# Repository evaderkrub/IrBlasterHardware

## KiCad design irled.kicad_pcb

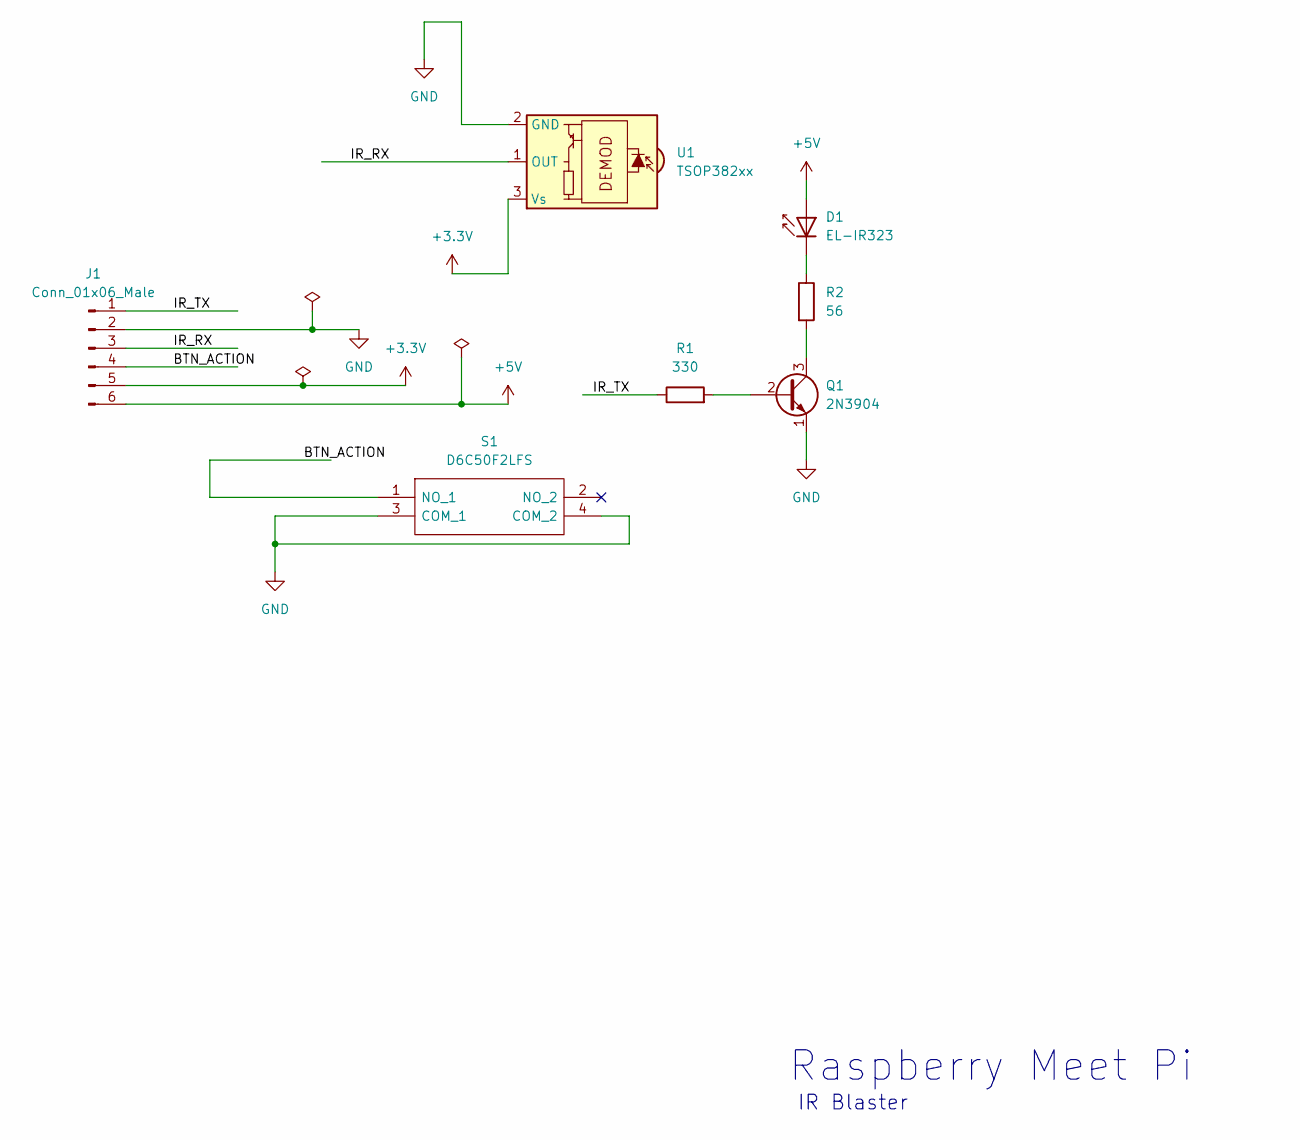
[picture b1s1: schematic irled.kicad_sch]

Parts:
D1: EL-IR323; LED_D5.0mm_IRGrey
J1: Conn_01x06_Male; PinHeader_1x06_P2.54mm_Vertical
Q1: 2N3904; TO-92_Inline
R1: 330; R_Axial_DIN0207_L6.3mm_D2.5mm_P10.16mm_Horizontal
R2: 56; R_Axial_DIN0309_L9.0mm_D3.2mm_P12.70mm_Horizontal
S1: D6C50F2LFS; Mouser Part Number 611-D6C50F2LFS
U1: TSOP382xx; Vishay_MINICAST-3Pin

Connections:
+3V3: J1.5, U1.3 (Vs)
+5V: D1.2 (A), J1.6
/BTN_ACTION: J1.4, S1.1 (NO_1)
/IR_RX: J1.3, U1.1 (OUT)
/IR_TX: J1.1, R1.1
GND: J1.2, Q1.1 (E), S1.3 (COM_1), S1.4 (COM_2), U1.2 (GND)
unnamed: D1.1 (K), R2.1
unnamed: Q1.2 (B), R1.2
unnamed: Q1.3 (C), R2.2

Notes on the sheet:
IR Blaster
Raspberry Meet Pi

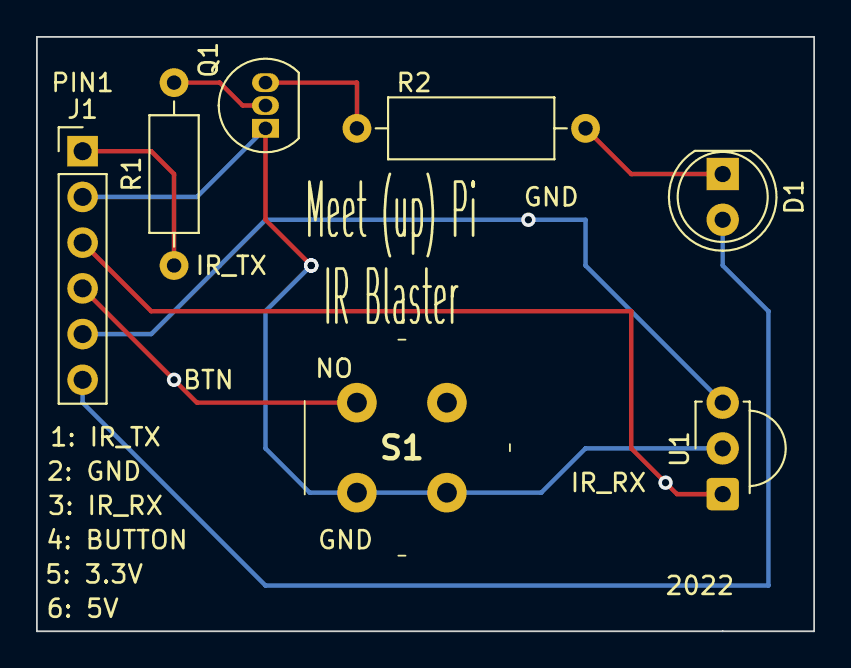
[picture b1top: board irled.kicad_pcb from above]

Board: 2 copper layers, 43.2 x 33.0 mm, 7 parts (0 on the bottom side), 9 nets.

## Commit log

2022-04-12 added pdf of schematic
